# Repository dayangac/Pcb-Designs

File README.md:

# Pcb-Designs

The PCB designs by Emre Dayangaç.

Current [favorite design](https://github.com/EmreDay1/Pcb-Designs/tree/main/FlowO) out of all the projects.

includes so ASIC's done in Verilog as well

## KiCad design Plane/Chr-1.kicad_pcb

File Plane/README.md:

pcb for research about wing angle and rpm

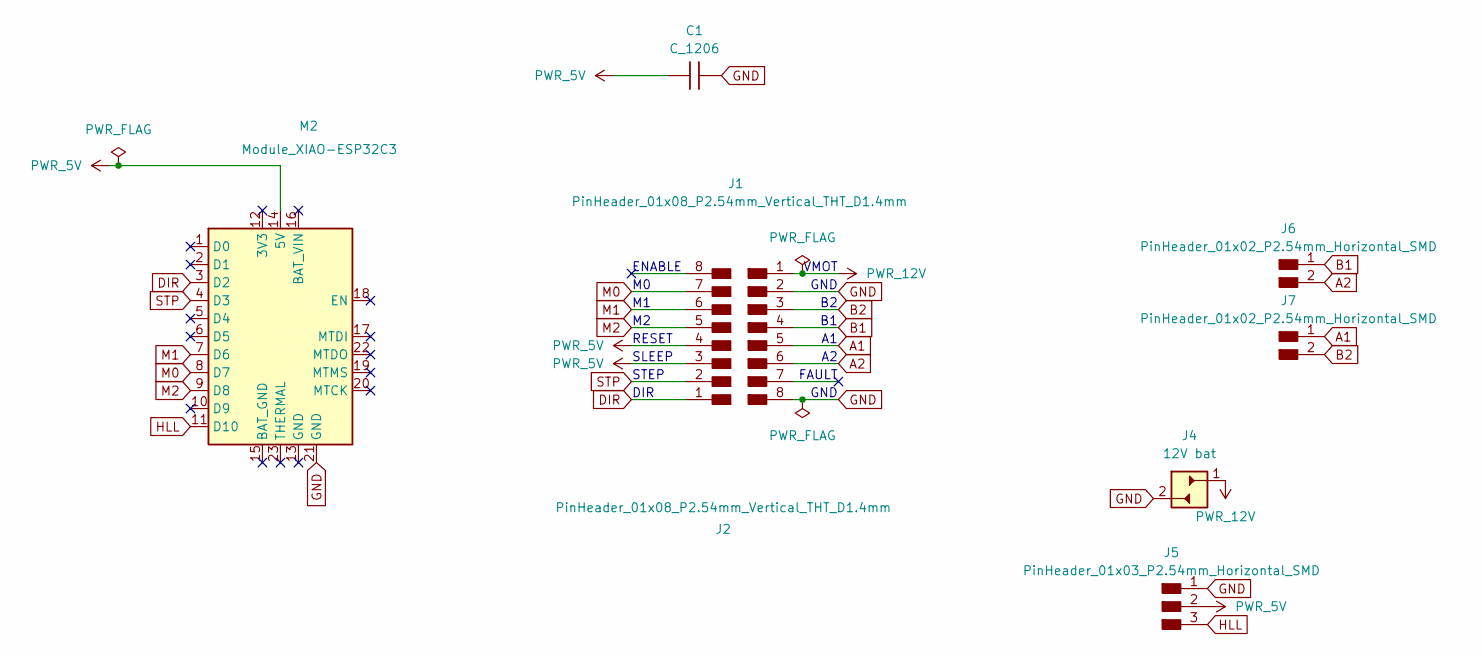
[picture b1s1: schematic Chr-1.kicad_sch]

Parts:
C1: C_1206
J1, J2: PinHeader_01x08_P2.54mm_Vertical_THT_D1.4mm; PinSocket_1x08_P1.00mm_Vertical_SMD_Pin1Left
J4: 12V bat; PinSocket_01x02_P2.54mm_Vertical_SMD
J5: PinHeader_01x03_P2.54mm_Horizontal_SMD
J6, J7: PinHeader_01x02_P2.54mm_Horizontal_SMD
M2: Module_XIAO-ESP32C3; SeeedStudio_XIAO_ESP32C3

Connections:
A1: J1.5, J7.1
A2: J1.6, J6.2
B1: J1.4, J6.1
B2: J1.3, J7.2
DIR: J2.1, M2.3 (D2)
GND: C1.2, J1.2, J1.8, J4.2, J5.1, M2.21 (GND)
HLL: J5.3, M2.11 (D10)
M0: J2.7, M2.8 (D7)
M1: J2.6, M2.7 (D6)
M2: J2.5, M2.9 (D8)
PWR_5V: C1.1, J2.3, J2.4, J5.2, M2.14 (5V)
PWR_12V: J1.1, J4.1
STP: J2.2, M2.4 (D3)

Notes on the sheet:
STEP
RESET
SLEEP
VMOT
ENABLE
FAULT
GND
DIR

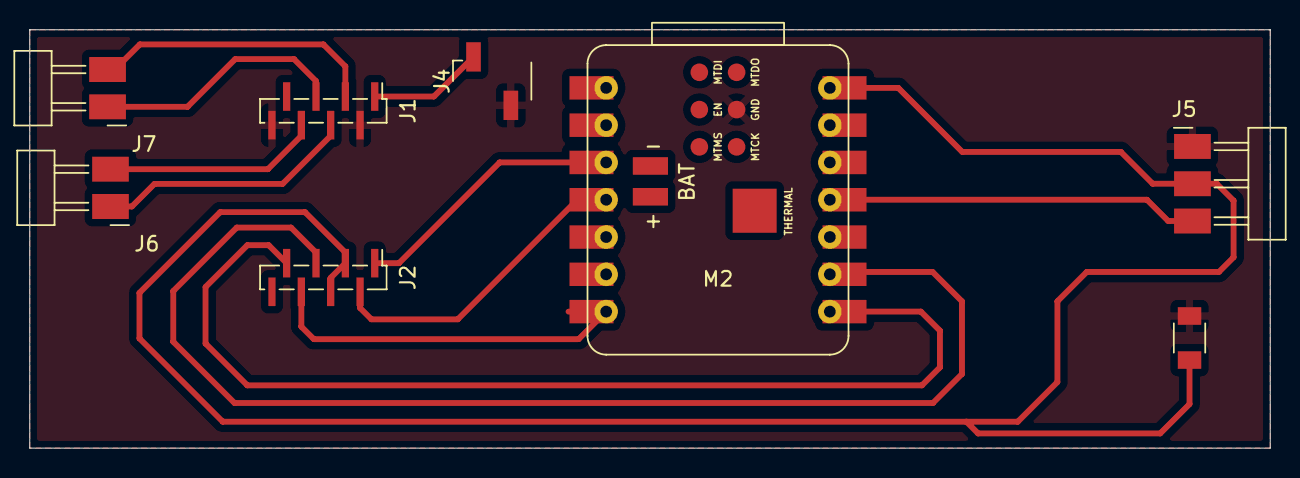
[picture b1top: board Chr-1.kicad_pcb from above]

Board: 2 copper layers, 84.5 x 28.5 mm, 8 parts (0 on the bottom side), 13 nets.

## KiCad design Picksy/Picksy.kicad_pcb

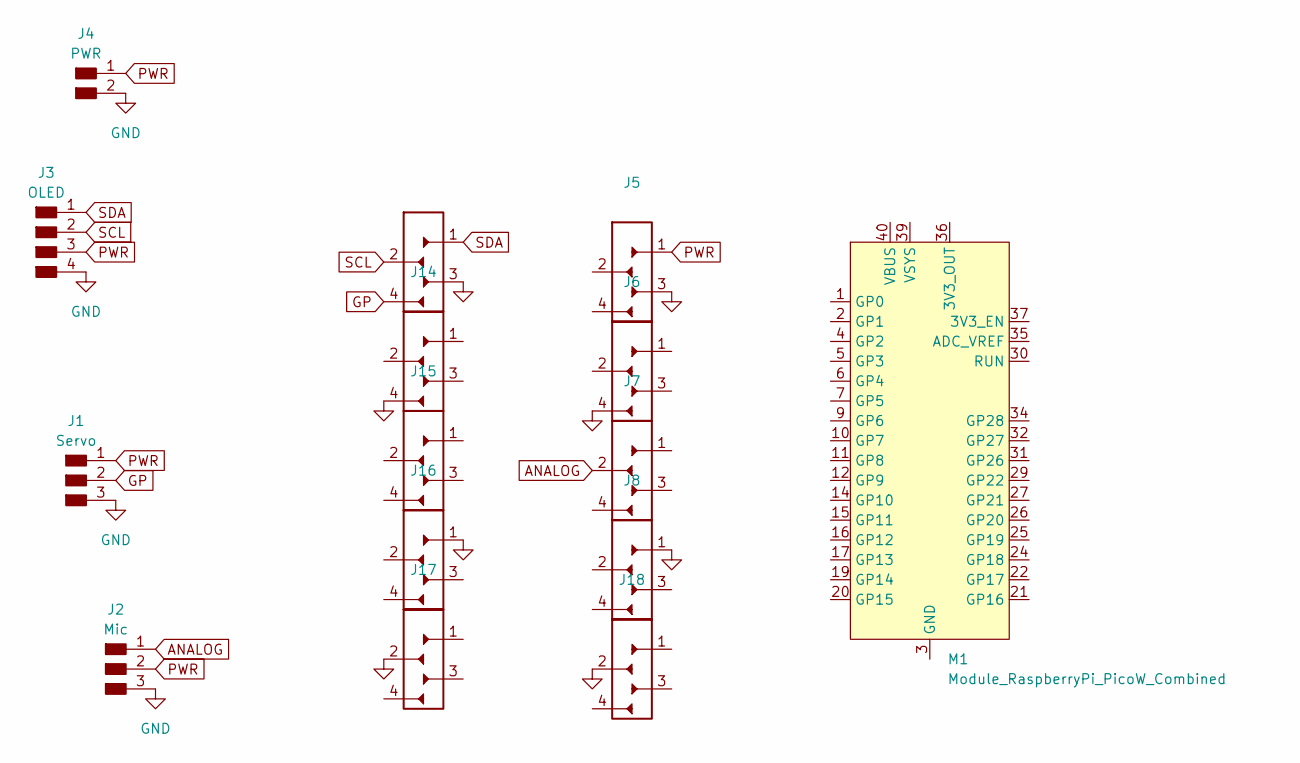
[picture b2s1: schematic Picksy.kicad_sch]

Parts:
J1: Servo; PinHeader_01x03_P2.54mm_Horizontal_SMD
J2: Mic; PinHeader_01x03_P2.54mm_Horizontal_SMD
J3: OLED; PinHeader_01x04_P2.54mm_Horizontal_SMD
J4: PWR; PinHeader_01x02_P2.54mm_Horizontal_SMD
J5, J6, J7, J8, J13, J14, J15, J16, J17, J18: PinSocket_01x04_P2.54mm_Vertical_SMD
M1: Module_RaspberryPi_PicoW_Combined; RaspberryPi_PicoW_Combined

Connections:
ANALOG: J2.1, J7.2
GND: J1.3, J2.3, J3.4, J4.2, J5.3 (Pin_1), J6.4 (Pin_2), J8.1, J13.3 (Pin_1), J14.4 (Pin_2), J16.1, J17.2, J18.2
GP: J1.2, J13.4 (Pin_2)
unnamed: M1.3 (GND), M1.8 (GND), M1.13 (GND), M1.18 (GND), M1.23 (GND), M1.28 (GND), M1.33 (GND), M1.38 (GND)
PWR: J1.1, J2.2, J3.3, J4.1, J5.1
SCL: J3.2, J13.2
SDA: J3.1, J13.1

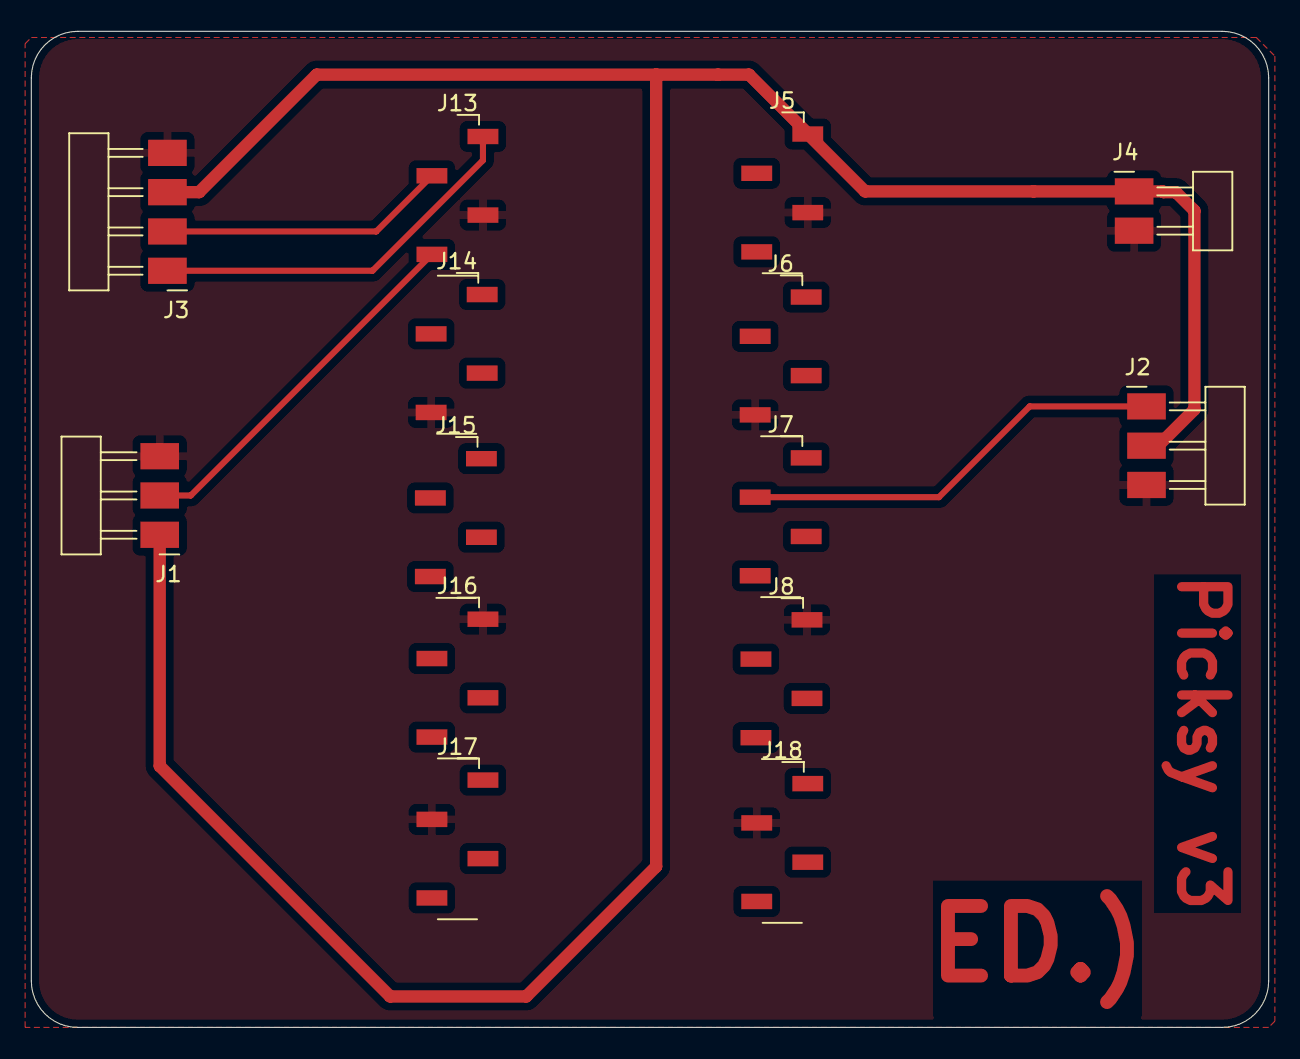
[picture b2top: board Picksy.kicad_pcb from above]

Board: 2 copper layers, 80.0 x 64.4 mm, 14 parts (0 on the bottom side), 6 nets.

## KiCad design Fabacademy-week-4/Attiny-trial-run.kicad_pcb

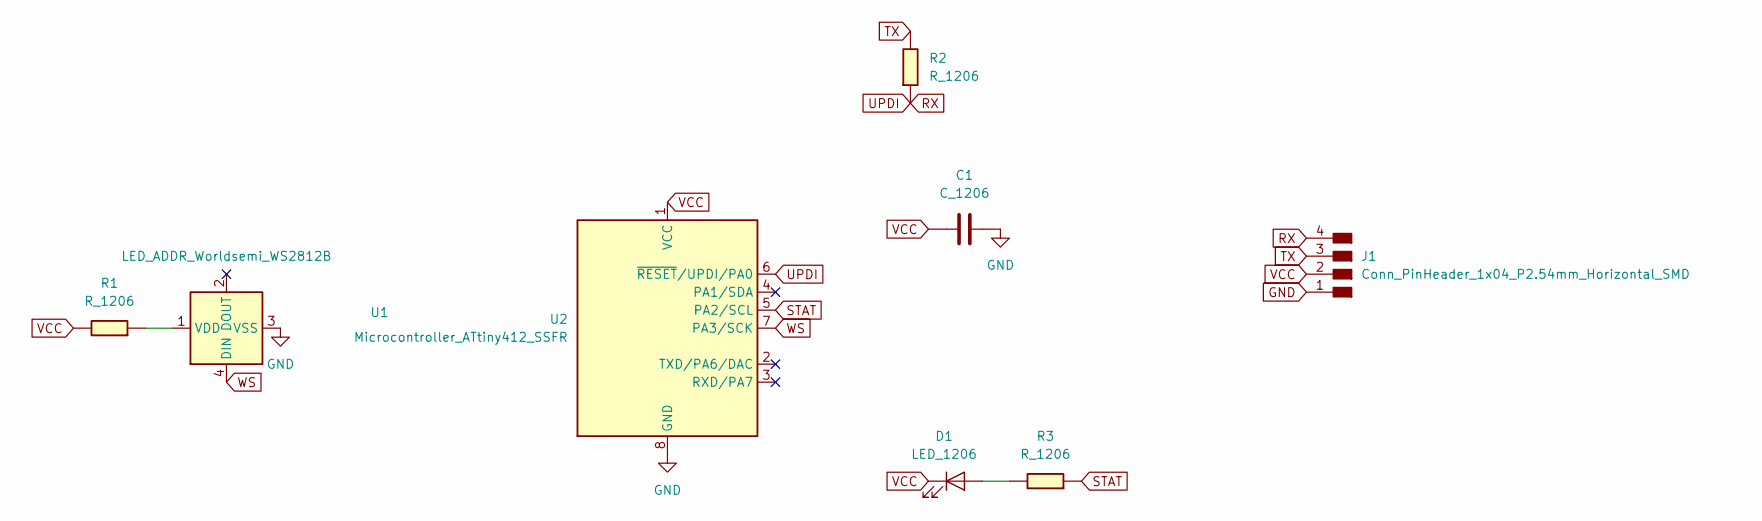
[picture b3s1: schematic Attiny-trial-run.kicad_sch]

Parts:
C1: C_1206
D1: LED_1206
J1: Conn_PinHeader_1x04_P2.54mm_Horizontal_SMD; PinHeader_01x04_P2.54mm_Horizontal_SMD
R1, R2, R3: R_1206
U1: LED_ADDR_Worldsemi_WS2812B
U2: Microcontroller_ATtiny412_SSFR; SOIC-8_3.9x4.9mm_P1.27mm

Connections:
GND: C1.2, J1.1, U1.3 (VSS), U2.8 (GND)
unnamed: D1.2 (A), R3.1
unnamed: R1.2, U1.1 (VDD)
RX: J1.4, R2.2, U2.6 (~RESET/UPDI/PA0)
STAT: R3.2, U2.5 (PA2/SCL)
TX: J1.3, R2.1
VCC: C1.1, D1.1 (K), J1.2, R1.1, U2.1 (VCC)
WS: U1.4 (DIN), U2.7 (PA3/SCK)

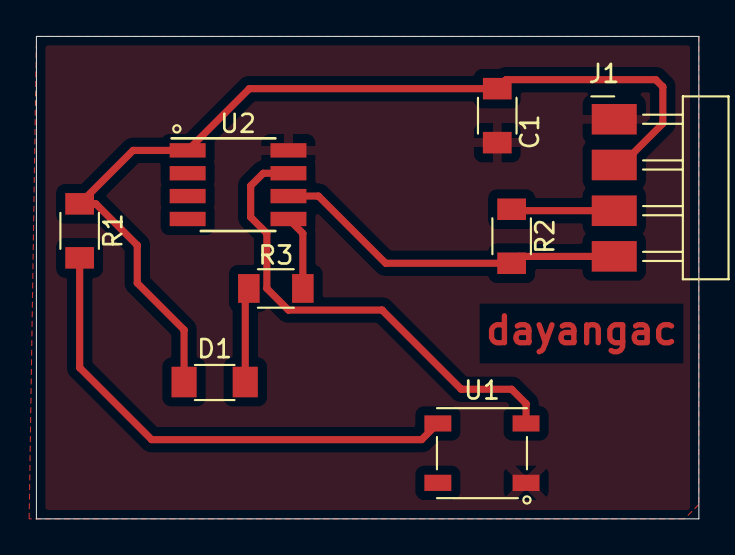
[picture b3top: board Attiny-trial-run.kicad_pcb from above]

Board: 2 copper layers, 36.8 x 26.8 mm, 8 parts (0 on the bottom side), 8 nets.

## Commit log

2025-11-01 picksy's pcb
2025-11-01 Add README for Application Specific Integrated Circuit
2025-11-01 Fix heading formatting in README.md
2025-12-01 Update README to include RPM in description
